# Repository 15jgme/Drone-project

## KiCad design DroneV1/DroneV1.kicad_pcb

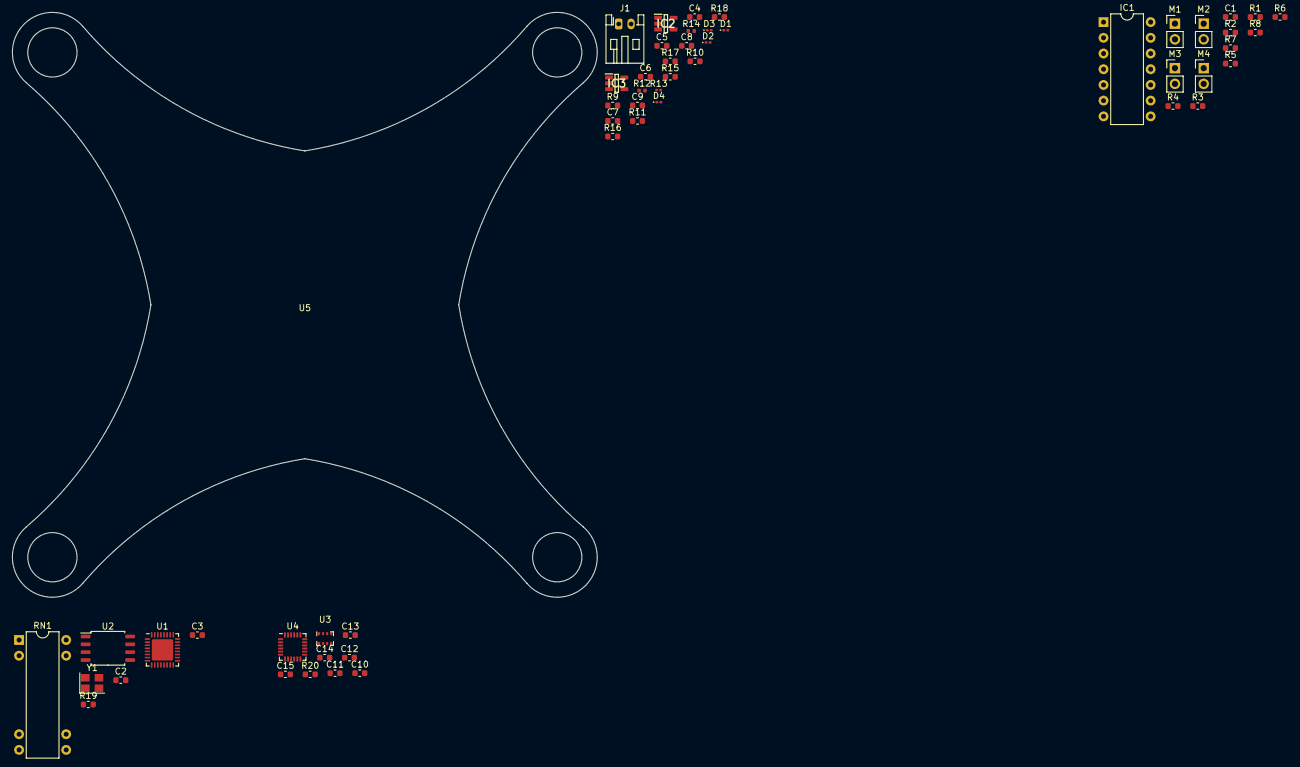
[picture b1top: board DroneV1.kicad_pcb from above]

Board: 2 copper layers, 94.6 x 94.6 mm, 54 parts (0 on the bottom side), 40 nets, no tracks yet.

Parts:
C1, C2, C3: C; C_0603_1608Metric
C4, C5, C8, C9: 1uF; C_0603_1608Metric
C6, C7: 22nF; C_0603_1608Metric
C10, C11, C13, C14: 100nF; C_0603_1608Metric
C12: 10nF; C_0603_1608Metric
C15: 2.2nF; C_0603_1608Metric
D1, D2, D3, D4: LED; LED_0201_0603Metric
IC1: 74HC14D,652; DIP-14_W7.62mm
IC2, IC3: RT9193-33GB; SOT94P279X130-5N
J1: Conn_01x02_Male; JST_PH_S2B-PH-K_1x02_P2.00mm_Horizontal
M1, M2, M3, M4: Motor_DC; PinHeader_1x02_P2.54mm_Vertical
R1, R2, R3, R4, R5, R6, R7, R8: 1k; R_0603_1608Metric
R9, R10: 1R; R_0603_1608Metric
R11, R15, R17: 10k; R_0603_1608Metric
R12, R14: 75R; R_0402_1005Metric
R13: 10k; R_0201_0603Metric
R16, R18: 47R; R_0603_1608Metric
R19: 200R; R_0603_1608Metric
R20: 4.7k; R_0603_1608Metric
RN1: R_Pack04; DIP-8-16_W7.62mm
U1: ESP8266EX; QFN-32-1EP_5x5mm_P0.5mm_EP3.45x3.45mm
U2: W25Q32JVSS; SOIC-8_5.23x5.23mm_P1.27mm
U3: BMP280; Bosch_LGA-8_2x2.5mm_P0.65mm_ClockwisePinNumbering
U4: MPU-6050; InvenSense_QFN-24_4x4mm_P0.5mm
U5: DroneOutline; DroneOutlineOLD
Y1: Crystal_GND24; Crystal_SMD_3225-4Pin_3.2x2.5mm

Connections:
+3V3: C12.1, C13.2, R9.1, R10.1, U2.8, U3.2, U4.8, U4.13
GND: C1.2, C3.2, C4.2, C5.2, C6.1, C7.1, C8.2, C9.2, C10.2, C11.1, C12.2, C13.1, C14.1, C15.1, IC1.7, IC2.2, IC3.2, J1.2, R1.2, R2.2, R3.2, R4.2, R5.1, R6.2, R7.2, R8.1, R11.2, R13.2, R15.2, R17.2, R20.2, U1.33, U2.4, U3.1, U3.5, U3.7, U4.1, U4.11, U4.18, Y1.4
M1: IC1.1, R1.1, RN1.5
M1B: IC1.2, R3.1
M2: IC1.3, R2.1, RN1.6
M2B: IC1.4, R4.1
M3: IC1.5, R5.2, RN1.7
M3B: IC1.6, R7.1
M4: IC1.9, R6.1, RN1.8
M4B: IC1.8, R8.2
unnamed: C2.1, Y1.2
unnamed: C2.2, U1.27, Y1.3
unnamed: C3.1, U1.28, Y1.1
unnamed: C6.2, IC2.4
unnamed: C7.2, IC3.4
unnamed: C8.1, IC2.5, R9.2
unnamed: C9.1, IC3.5, R10.2
unnamed: C14.2, U4.10
unnamed: C15.2, U4.20
unnamed: D1.2, R12.1
unnamed: D2.2, R14.1
unnamed: D3.2, R16.2
unnamed: D4.2, R18.2
unnamed: R19.2, U1.21
unnamed: R20.1, U4.9
unnamed: RN1.1, U1.9
unnamed: RN1.2, U1.13
unnamed: RN1.3, U1.10
unnamed: RN1.4, U1.16
SCL: U3.4, U4.23
SDA: U3.3, U4.24
SDIO_CLK: R19.1, U2.6
SDIO_CMD: U1.20, U2.1
SDIO_SD0: U1.22, U2.2
SDIO_SD1: U1.23, U2.5
SDIO_SD2: U1.18, U2.7
SDIO_SD3: U1.19, U2.3
VBUS: C1.1, C4.1, C5.1, C10.1, C11.2, IC1.14, IC2.1, IC2.3, IC3.1, IC3.3, J1.1, R12.2, R14.2, R16.1, R18.1, U3.6, U3.8
ledGreen: R15.1, R17.1
ledRed: R11.1, R13.1

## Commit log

2019-12-23 Added working files
2019-12-23 Added sensors, power regulation
2019-12-24 Added indicator LEDs
